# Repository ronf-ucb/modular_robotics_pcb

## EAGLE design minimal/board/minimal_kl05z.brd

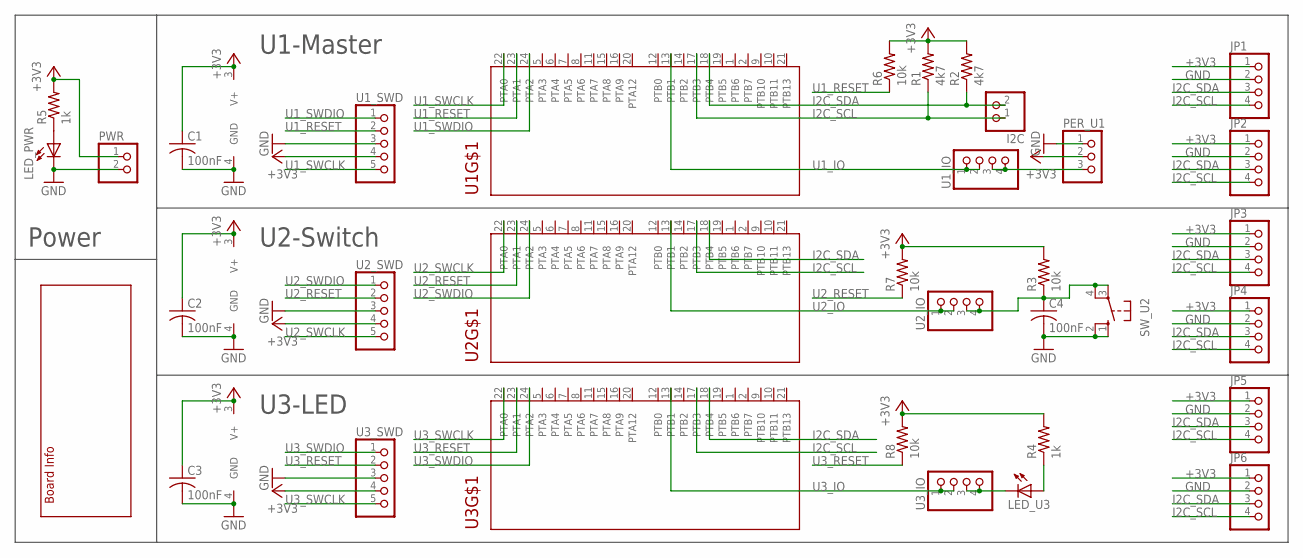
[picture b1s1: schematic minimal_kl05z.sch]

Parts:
C1, C2, C3, C4: 100nF; C025-025X050
I2C: PINHD-1X2; 1X02
JP1, JP2, JP3, JP4, JP5, JP6: PINHD-1X4; 1X04
LED_PWR: LED5MM
LED_U3: LED5MM
PER_U1: PINHD-1X3; 1X03
PWR: PINHD-1X2; 1X02
R1, R2: 4k7; 0204/7
R3: 10k; 0204V
R4, R5: 1k; 0204V
R6, R7, R8: 10k; 0204/7
SW_U2: 10-XX; B3F-10XX
U1, U2, U3: MKL05Z32VFK4-DIP; DIL24-3
U1_IO, U2_IO, U3_IO: PINHD-1X4; 1X04
U1_SWD, U2_SWD, U3_SWD: PINHD-1X5; 1X05
U$1: INFO

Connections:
+3V3: C1.1, C2.1, C3.1, JP1.1, JP2.1, JP3.1, JP4.1, JP5.1, JP6.1, PER_U1.2, PWR.1, R1.2, R2.2, R3.2, R4.2, R5.2, R6.2, R7.2, R8.2, U1.3 (V+), U1_SWD.4, U2.3 (V+), U2_SWD.4, U3.3 (V+), U3_SWD.4
GND: C1.2, C2.2, C3.2, C4.2, JP1.2, JP2.2, JP3.2, JP4.2, JP5.2, JP6.2, LED_PWR.K (C), PER_U1.1, PWR.2, SW_U2.1 (S), SW_U2.2 (S1), U1.4 (GND), U1_SWD.3, U2.4 (GND), U2_SWD.3, U3.4 (GND), U3_SWD.3
I2C_SCL: I2C.1, JP1.4, JP2.4, JP3.4, JP4.4, JP5.4, JP6.4, R1.1, U1.17 (PTB3), U2.17 (PTB3), U3.17 (PTB3)
I2C_SDA: I2C.2, JP1.3, JP2.3, JP3.3, JP4.3, JP5.3, JP6.3, R2.1, U1.18 (PTB4), U2.18 (PTB4), U3.18 (PTB4)
unnamed: LED_PWR.A, R5.1
unnamed: C4.1, R3.1, SW_U2.3, SW_U2.4 (P1), U2_IO.3, U2_IO.4
unnamed: PER_U1.3, U1_IO.3, U1_IO.4
unnamed: LED_U3.A, R4.1
unnamed: LED_U3.K (C), U3_IO.3, U3_IO.4
U1_IO: U1.13 (PTB1), U1_IO.1, U1_IO.2
U1_RESET: R6.1, U1.23 (PTA1), U1_SWD.2
U1_SWCLK: U1.22 (PTA0), U1_SWD.5
U1_SWDIO: U1.24 (PTA2), U1_SWD.1
U2_IO: U2.13 (PTB1), U2_IO.1, U2_IO.2
U2_RESET: R7.1, U2.23 (PTA1), U2_SWD.2
U2_SWCLK: U2.22 (PTA0), U2_SWD.5
U2_SWDIO: U2.24 (PTA2), U2_SWD.1
U3_IO: U3.13 (PTB1), U3_IO.1, U3_IO.2
U3_RESET: R8.1, U3.23 (PTA1), U3_SWD.2
U3_SWCLK: U3.22 (PTA0), U3_SWD.5
U3_SWDIO: U3.24 (PTA2), U3_SWD.1

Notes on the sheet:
U1-Master
U2-Switch
U3-LED
Power

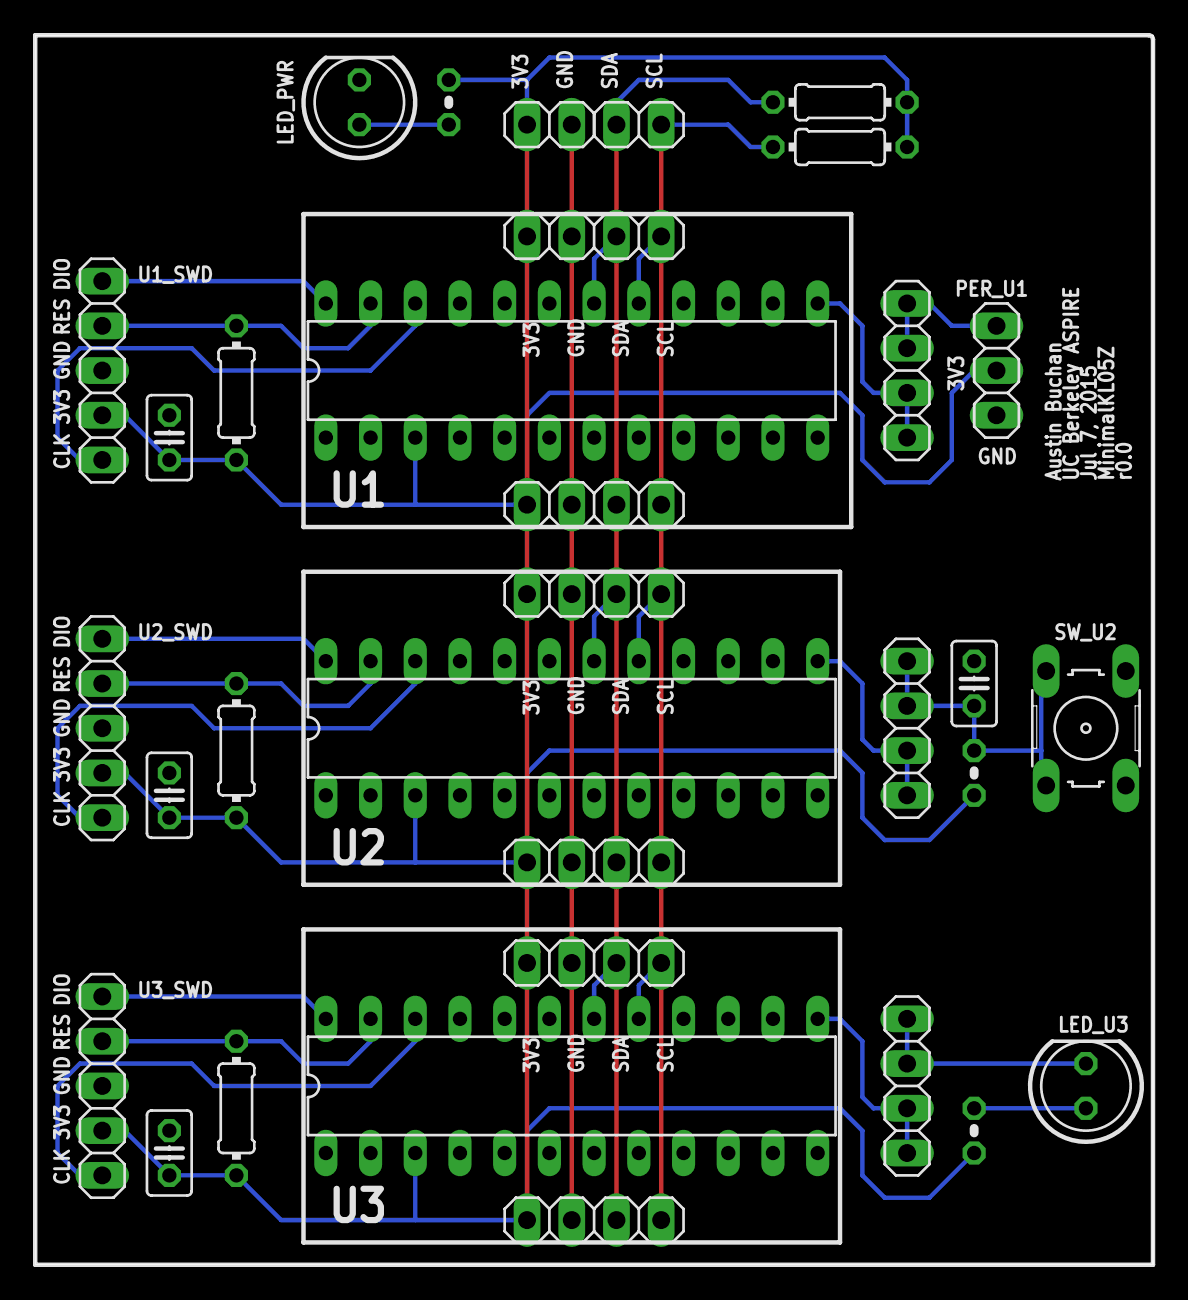
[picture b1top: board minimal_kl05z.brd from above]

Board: 2 copper layers, 63.5 x 69.8 mm, 34 parts (0 on the bottom side), 21 nets.

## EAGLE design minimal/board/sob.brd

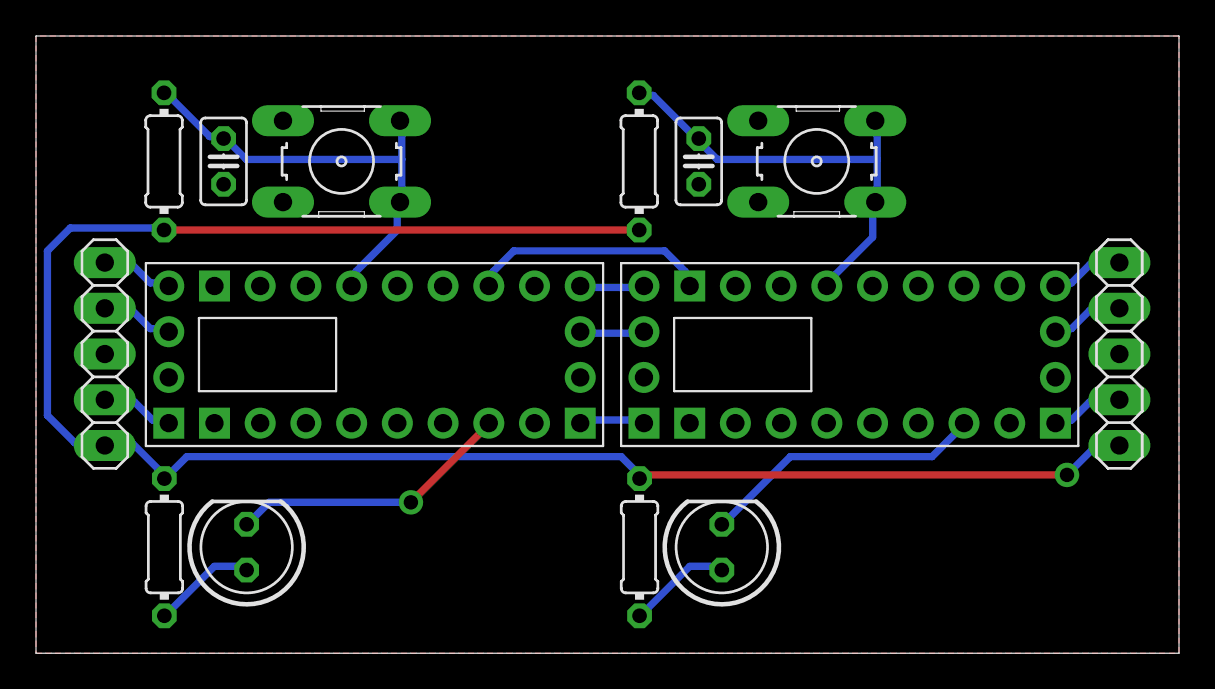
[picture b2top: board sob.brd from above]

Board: 2 copper layers, 63.5 x 34.3 mm, 14 parts (0 on the bottom side), 18 nets.

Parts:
C545, C622: 100nf; C025-025X050
CPU221, CPU610: CARRIER_DIP
LED552, LED629: LED5MM
R439, R597, R621, R630: 1k; 0204/7
SW339, SW620: B3F-10XX
SWD_L16: 1X05
SWD_R219: 1X05

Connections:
GND655: C545.1, C622.1, CPU221.GND_0, CPU221.GND_1, CPU221.PTB0, CPU610.GND_0, CPU610.GND_1, SW339.2, SW339.4, SW620.2, SW620.4, SWD_L16.3, SWD_R219.3
IO550: C545.2, CPU221.PTB5, R439.1, SW339.1, SW339.3
IO603: CPU221.PTB10, LED552.K
IO627: C622.2, CPU610.PTB5, R621.1, SW620.1, SW620.3
IO636: CPU610.PTB10, LED629.K
SCL01649: CPU221.SCL_1, CPU610.SCL_0
SCL_L643: CPU221.SCL_0, SWD_L16.4
SCL_R646: CPU610.SCL_1, SWD_R219.4
SDA01650: CPU221.SDA_1, CPU610.SDA_0
SDA_L644: CPU221.SDA_0, SWD_L16.5
SDA_R647: CPU610.SDA_1, SWD_R219.5
TOK01651: CPU221.PTB2, CPU610.PTB0
UP598: LED552.A, R597.1
UP631: LED629.A, R630.1
V3653: R439.2, R597.2, R621.2, R630.2, SWD_L16.1, SWD_R219.1
VCC01648: CPU221.VCC_1, CPU610.VCC_0
VCC_L642: CPU221.VCC_0, SWD_L16.2
VCC_R645: CPU610.VCC_1, SWD_R219.2

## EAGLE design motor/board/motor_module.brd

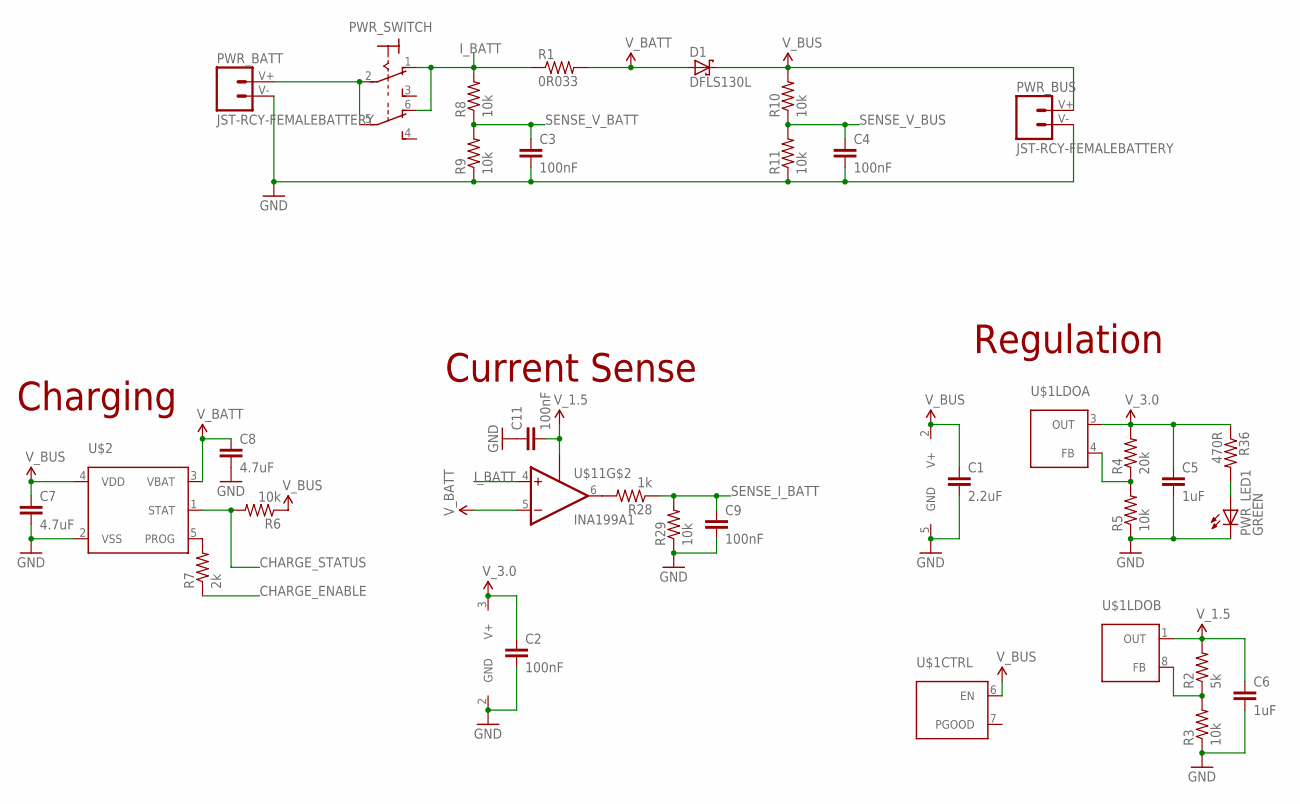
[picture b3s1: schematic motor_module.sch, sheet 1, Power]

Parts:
C1: 2.2uF; 0402-CAP
C2, C3, C4, C9, C11: 100nF; 0402-CAP
C5, C6: 1uF; 0402-CAP
C7, C8: 4.7uF; 0402-CAP
D1: DFLS130L; POWERDI123
PWR_BATT: JST-RCY-FEMALEBATTERY; TP_LIPO_160MAH
PWR_BUS: JST-RCY-FEMALEBATTERY; TP_LIPO_160MAH
PWR_LED1: GREEN; LED-0603
PWR_SWITCH: JS202011SCQN
R1: 0R033; 0603-RES
R2: 5k; 0402-RES
R3, R5, R6, R8, R9, R10, R11, R29: 10k; 0402-RES
R4: 20k; 0402-RES
R7: 2k; 0402-RES
R28: 1k; 0402-RES
R36: 470R; 0402-RES
U$1: SC560C; MLPQ-UT8
U$2: MCP73831T; SOT23-5
U$11: INA199A1; SC70-6

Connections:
CHARGE_ENABLE: R7.1; also elsewhere on the board
CHARGE_STATUS: R6.2, U$2.1 (STAT); also elsewhere on the board
GND: C1.2, C2.2, C3.2, C4.2, C5.2, C6.2, C7.2, C8.2, C9.2, C11.1, PWR_BATT.V- (1), PWR_BUS.V- (1), PWR_LED1.C, R3.1, R5.1, R9.1, R11.1, R29.1, U$1.5 (GND), U$2.2 (VSS), U$11.2 (GND); also elsewhere on the board
I_BATT: PWR_SWITCH.1 (O), PWR_SWITCH.6 (O), R1.1, R8.2, U$11.4 (+IN)
unnamed: PWR_BATT.V+ (2), PWR_SWITCH.2, PWR_SWITCH.5
unnamed: R2.1, R3.2, U$1.8 (FB)
unnamed: R4.1, R5.2, U$1.4 (FB)
unnamed: R7.2, U$2.5 (PROG)
unnamed: R28.2, U$11.6 (OUT)
unnamed: PWR_LED1.A, R36.2
SENSE_I_BATT: C9.1, R28.1, R29.2; also elsewhere on the board
SENSE_V_BATT: C3.1, R8.1, R9.2; also elsewhere on the board
SENSE_V_BUS: C4.1, R10.1, R11.2; also elsewhere on the board
V_1.5: C6.1, C11.2, R2.2, U$1.1 (OUT), U$11.1 (REF); also elsewhere on the board
V_3.0: C2.1, C5.1, R4.2, R36.1, U$1.3 (OUT), U$11.3 (V+); also elsewhere on the board
V_BATT: C8.1, D1.A, R1.2, U$2.3 (VBAT), U$11.5 (-IN); also elsewhere on the board
V_BUS: C1.1, C7.1, D1.C, PWR_BUS.V+ (2), R6.1, R10.2, U$1.2 (V+), U$1.6 (EN), U$2.4 (VDD)

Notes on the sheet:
Charging
Current Sense
Regulation

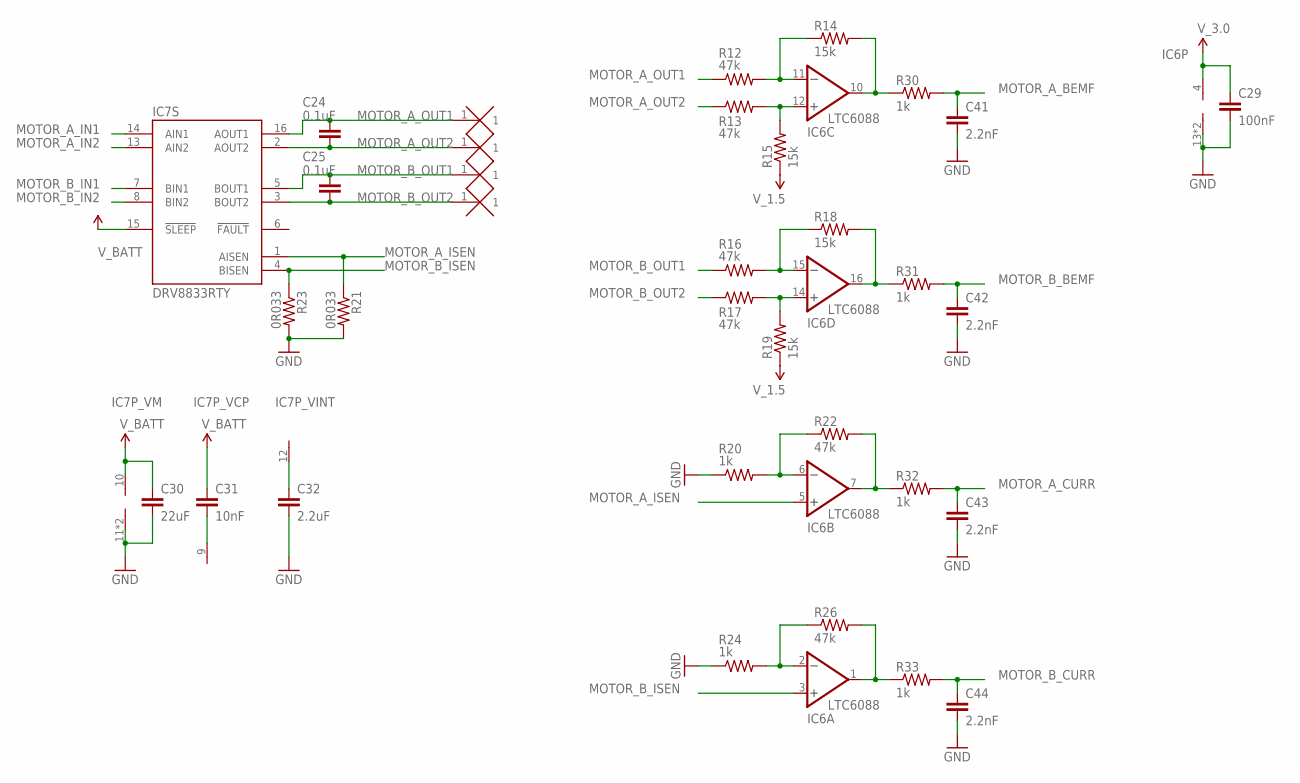
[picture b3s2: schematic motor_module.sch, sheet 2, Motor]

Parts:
C24, C25: 0.1uF; 0402-CAP; VOLTAGE 10V
C29: 100nF; 0402-CAP
C30: 22uF; 0603-CAP
C31: 10nF; 0402-CAP; VOLTAGE 16V
C32: 2.2uF; 0402-CAP; VOLTAGE 6.3V
C41, C42, C43, C44: 2.2nF; 0402-CAP
IC6: LTC6088; DFN-16
IC7: DRV8833RTY; S-PWQFN-N16
MA1, MA2: PAD-0.6_1.8; PAD_0.6_1.8
MB1, MB2: PAD-0.6_1.8; PAD_0.6_1.8
R12, R13, R16, R17, R22, R26: 47k; 0402-RES; TOLERANCE 1%
R14, R15, R18, R19: 15k; 0402-RES; TOLERANCE 1%
R20, R24: 1k; 0402-RES; TOLERANCE 1%
R21, R23: 0R033; 0603-RES
R30, R31, R32, R33: 1k; 0402-RES

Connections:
GND: C29.2, C30.2, C32.2, C41.2, C42.2, C43.2, C44.2, IC6.13 (V-), IC6.PAD (V-), IC7.11 (V-), IC7.PPAD (V-), R20.1, R21.2, R23.2, R24.1; also elsewhere on the board
MOTOR_A_BEMF: C41.1, R30.2; also elsewhere on the board
MOTOR_A_CURR: C43.1, R32.2; also elsewhere on the board
MOTOR_A_IN1: IC7.14 (AIN1); also elsewhere on the board
MOTOR_A_IN2: IC7.13 (AIN2); also elsewhere on the board
MOTOR_A_ISEN: IC6.5 (+IN), IC7.1 (AISEN), R21.1
MOTOR_A_OUT1: C24.1, IC7.16 (AOUT1), MA1.1, R12.1
MOTOR_A_OUT2: C24.2, IC7.2 (AOUT2), MA2.1, R13.1
MOTOR_B_BEMF: C42.1, R31.2; also elsewhere on the board
MOTOR_B_CURR: C44.1, R33.2; also elsewhere on the board
MOTOR_B_IN1: IC7.7 (BIN1); also elsewhere on the board
MOTOR_B_IN2: IC7.8 (BIN2); also elsewhere on the board
MOTOR_B_ISEN: IC6.3 (+IN), IC7.4 (BISEN), R23.1
MOTOR_B_OUT1: C25.1, IC7.5 (BOUT1), MB1.1, R16.1
MOTOR_B_OUT2: C25.2, IC7.3 (BOUT2), MB2.1, R17.1
unnamed: C31.2, IC7.9 (V+)
unnamed: C32.1, IC7.12 (V-)
unnamed: IC6.15 (-IN), R16.2, R18.1
unnamed: IC6.14 (+IN), R17.2, R19.2
unnamed: IC6.6 (-IN), R20.2, R22.1
unnamed: IC6.2 (-IN), R24.2, R26.1
unnamed: IC6.11 (-IN), R12.2, R14.1
unnamed: IC6.12 (+IN), R13.2, R15.2
unnamed: IC6.1 (OUT), R26.2, R33.1
unnamed: IC6.7 (OUT), R22.2, R32.1
unnamed: IC6.10 (OUT), R14.2, R30.1
unnamed: IC6.16 (OUT), R18.2, R31.1
V_1.5: R15.1, R19.1; also elsewhere on the board
V_3.0: C29.1, IC6.4 (V+); also elsewhere on the board
V_BATT: C30.1, C31.1, IC7.10 (V+), IC7.15 (!SLEEP); also elsewhere on the board

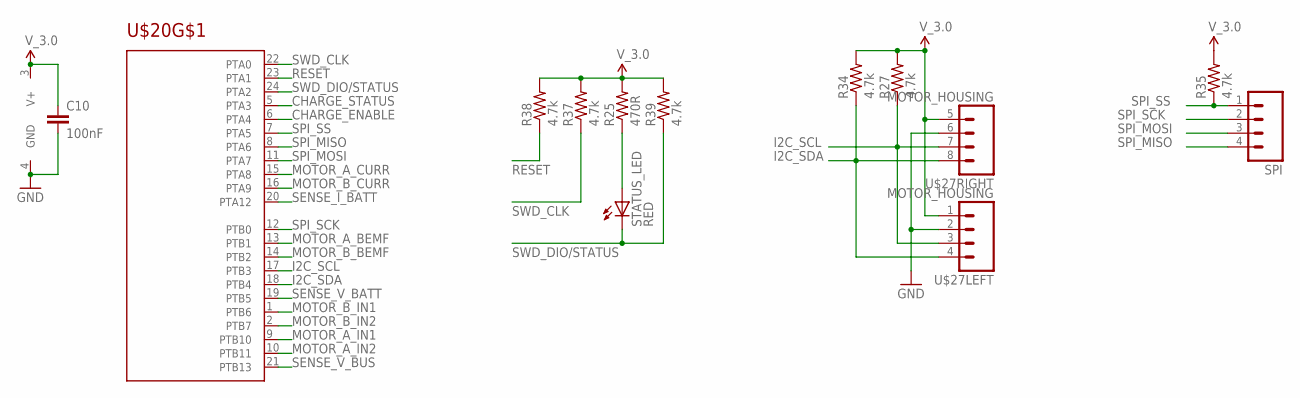
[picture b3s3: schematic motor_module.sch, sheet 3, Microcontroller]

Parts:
C10: 100nF; 0402-CAP
R25: 470R; 0402-RES
R27, R34, R35, R37, R38, R39: 4.7k; 0402-RES
SPI: M04FFC; MOLEX_503480-0400
STATUS_LED: RED; LED-0603
U$20: MKL05Z32VFK4; QFN-24
U$27: MOTOR_HOUSING

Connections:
CHARGE_ENABLE: U$20.6 (PTA4); also elsewhere on the board
CHARGE_STATUS: U$20.5 (PTA3); also elsewhere on the board
GND: C10.2, U$20.4 (GND), U$27.2, U$27.6 (2); also elsewhere on the board
I2C_SCL: R27.1, U$20.17 (PTB3), U$27.3, U$27.7 (3)
I2C_SDA: R34.1, U$20.18 (PTB4), U$27.4, U$27.8 (4)
MOTOR_A_BEMF: U$20.13 (PTB1); also elsewhere on the board
MOTOR_A_CURR: U$20.15 (PTA8); also elsewhere on the board
MOTOR_A_IN1: U$20.9 (PTB10); also elsewhere on the board
MOTOR_A_IN2: U$20.10 (PTB11); also elsewhere on the board
MOTOR_B_BEMF: U$20.14 (PTB2); also elsewhere on the board
MOTOR_B_CURR: U$20.16 (PTA9); also elsewhere on the board
MOTOR_B_IN1: U$20.1 (PTB6); also elsewhere on the board
MOTOR_B_IN2: U$20.2 (PTB7); also elsewhere on the board
unnamed: R25.1, STATUS_LED.A
RESET: R38.1, U$20.23 (PTA1)
SENSE_I_BATT: U$20.20 (PTA12); also elsewhere on the board
SENSE_V_BATT: U$20.19 (PTB5); also elsewhere on the board
SENSE_V_BUS: U$20.21 (PTB13); also elsewhere on the board
SPI_MISO: SPI.4, U$20.8 (PTA6)
SPI_MOSI: SPI.3, U$20.11 (PTA7)
SPI_SCK: SPI.2, U$20.12 (PTB0)
SPI_SS: R35.1, SPI.1, U$20.7 (PTA5)
SWD_CLK: R37.1, U$20.22 (PTA0)
SWD_DIO/STATUS: R39.1, STATUS_LED.C, U$20.24 (PTA2)
V_3.0: C10.1, R25.2, R27.2, R34.2, R35.2, R37.2, R38.2, R39.2, U$20.3 (V+), U$27.1, U$27.5 (1); also elsewhere on the board

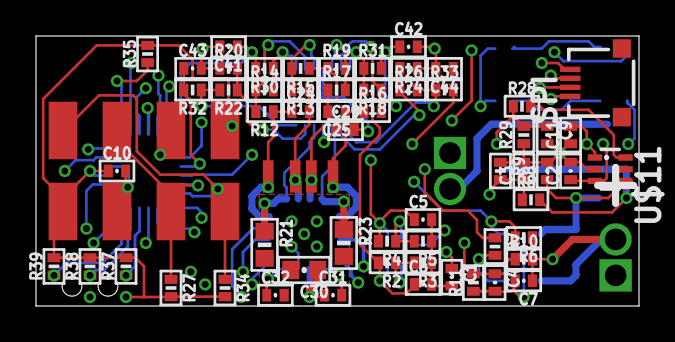
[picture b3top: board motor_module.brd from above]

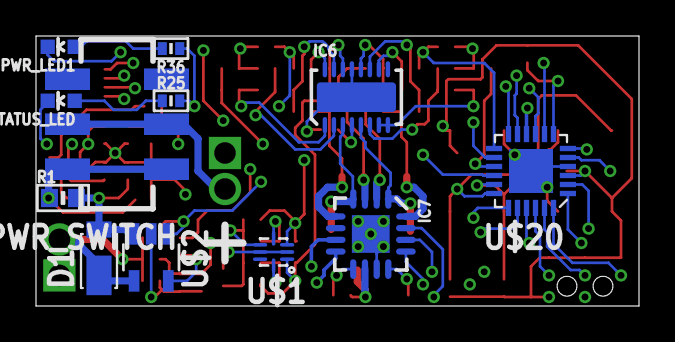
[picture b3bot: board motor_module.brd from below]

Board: 4 copper layers, 33.5 x 15.0 mm, 78 parts (13 on the bottom side), 53 nets.

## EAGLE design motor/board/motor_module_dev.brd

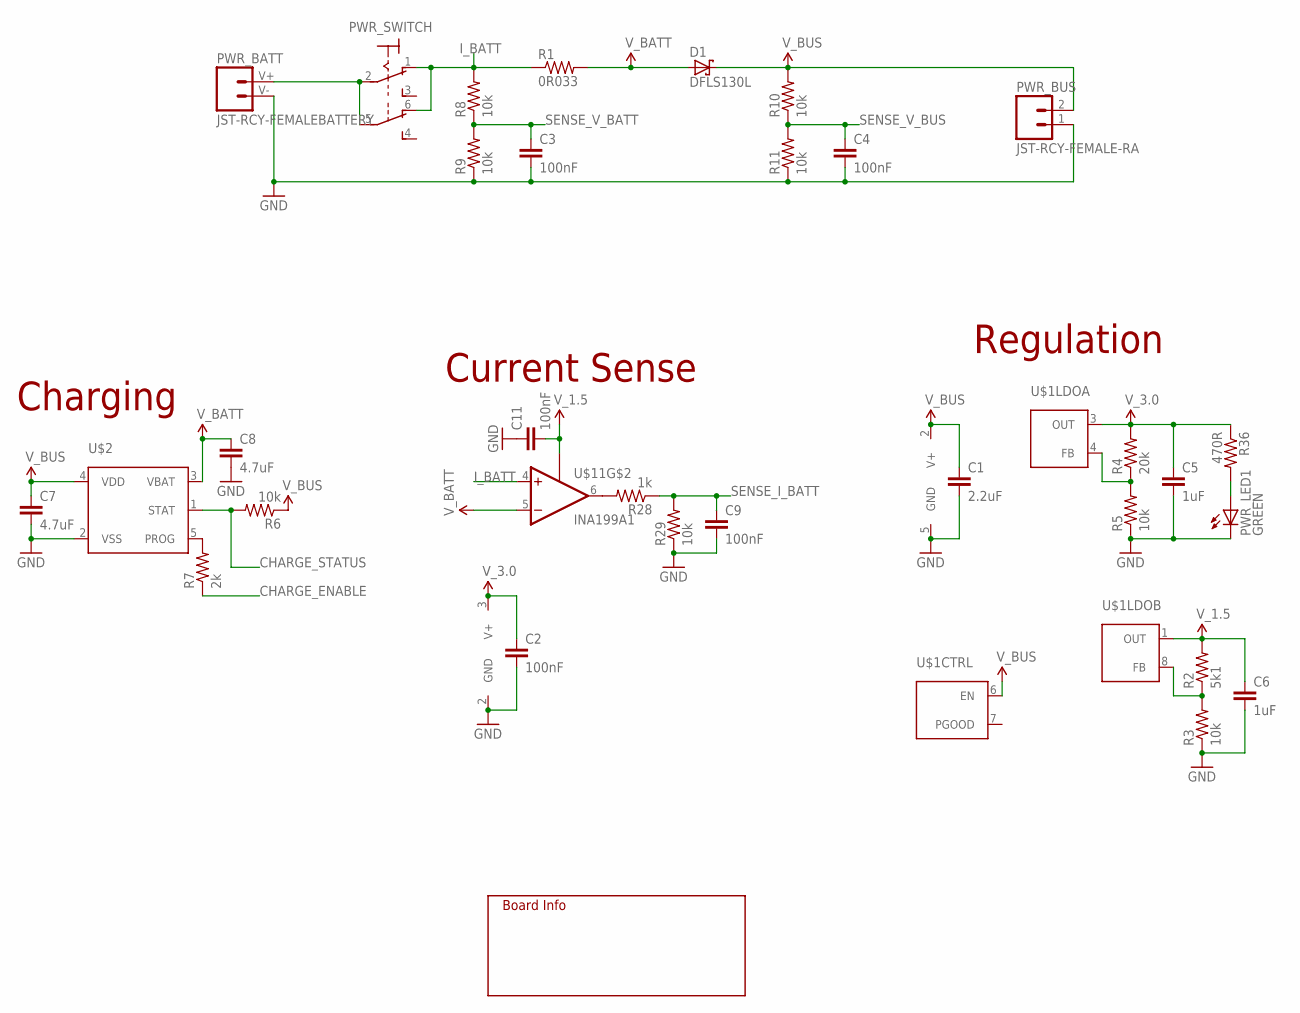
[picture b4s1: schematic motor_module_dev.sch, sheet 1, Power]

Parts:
C1: 2.2uF; 0402-CAP; VOLTAGE 10V
C2, C3, C4, C9, C11: 100nF; 0402-CAP; VOLTAGE 6.3V
C5, C6: 1uF; 0402-CAP; VOLTAGE 6.3V
C7, C8: 4.7uF; 0402-CAP; VOLTAGE 10V
D1: DFLS130L; POWERDI123
PWR_BATT: JST-RCY-FEMALEBATTERY; TP_LIPO_160MAH
PWR_BUS: JST-RCY-FEMALE-RA; JST_2_FEMALE
PWR_LED1: GREEN; LED-0603
PWR_SWITCH: JS202011SCQN
R1: 0R033; 0603-RES
R2: 5k1; 0402-RES
R3, R5, R6, R8, R9, R10, R11, R29: 10k; 0402-RES
R4: 20k; 0402-RES
R7: 2k; 0402-RES
R28: 1k; 0402-RES
R36: 470R; 0402-RES
U$1: SC560C; MLPQ-UT8
U$2: MCP73831T; SOT23-5
U$11: INA199A1; SC70-6
U$31: INFO

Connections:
CHARGE_ENABLE: R7.1; also elsewhere on the board
CHARGE_STATUS: R6.2, U$2.1 (STAT); also elsewhere on the board
GND: C1.2, C2.2, C3.2, C4.2, C5.2, C6.2, C7.2, C8.2, C9.2, C11.1, PWR_BATT.V- (1), PWR_BUS.1, PWR_LED1.C, R3.1, R5.1, R9.1, R11.1, R29.1, U$1.5 (GND), U$2.2 (VSS), U$11.2 (GND); also elsewhere on the board
I_BATT: PWR_SWITCH.1 (O), PWR_SWITCH.6 (O), R1.1, R8.2, U$11.4 (+IN)
unnamed: PWR_BATT.V+ (2), PWR_SWITCH.2, PWR_SWITCH.5
unnamed: R2.1, R3.2, U$1.8 (FB)
unnamed: R4.1, R5.2, U$1.4 (FB)
unnamed: R7.2, U$2.5 (PROG)
unnamed: R28.2, U$11.6 (OUT)
unnamed: PWR_LED1.A, R36.2
SENSE_I_BATT: C9.1, R28.1, R29.2; also elsewhere on the board
SENSE_V_BATT: C3.1, R8.1, R9.2; also elsewhere on the board
SENSE_V_BUS: C4.1, R10.1, R11.2; also elsewhere on the board
V_1.5: C6.1, C11.2, R2.2, U$1.1 (OUT), U$11.1 (REF); also elsewhere on the board
V_3.0: C2.1, C5.1, R4.2, R36.1, U$1.3 (OUT), U$11.3 (V+); also elsewhere on the board
V_BATT: C8.1, D1.A, R1.2, U$2.3 (VBAT), U$11.5 (-IN); also elsewhere on the board
V_BUS: C1.1, C7.1, D1.C, PWR_BUS.2, R6.1, R10.2, U$1.2 (V+), U$1.6 (EN), U$2.4 (VDD); also elsewhere on the board

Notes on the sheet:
Charging
Current Sense
Regulation

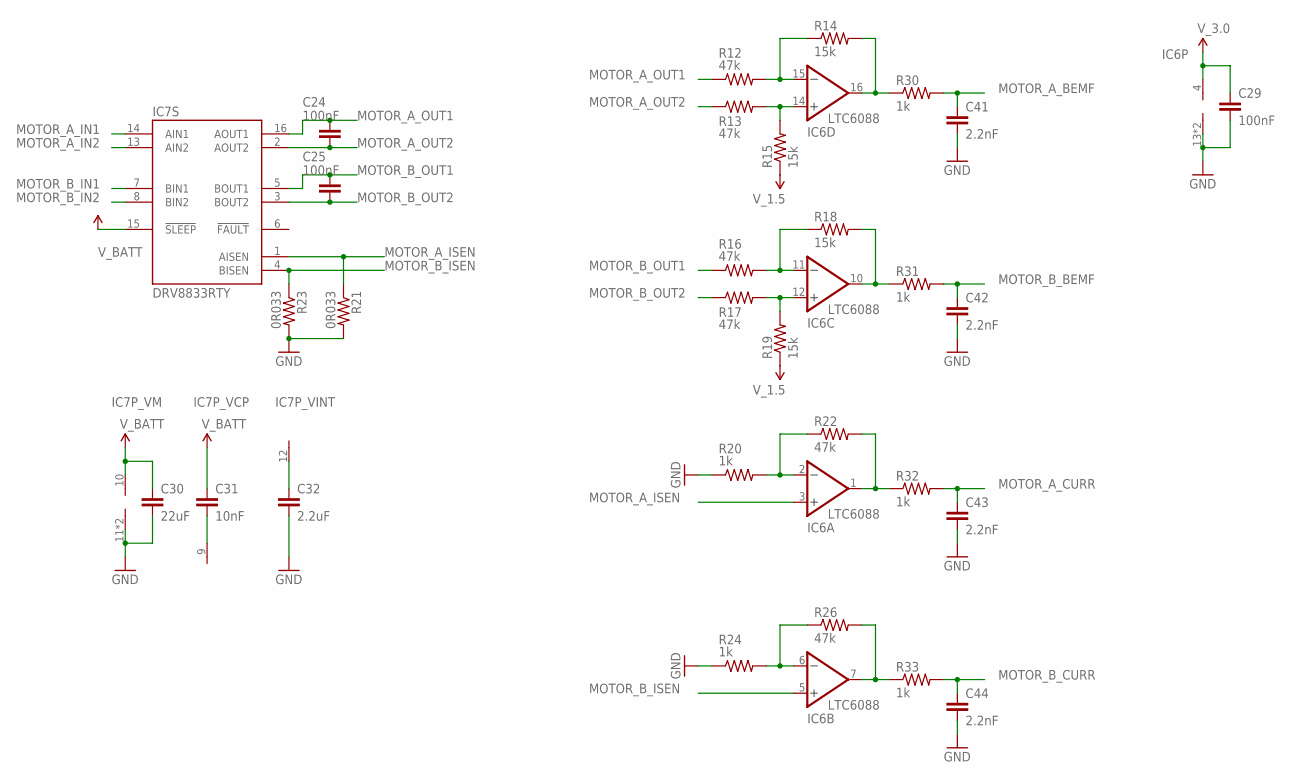
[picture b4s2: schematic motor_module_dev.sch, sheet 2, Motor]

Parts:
C24, C25: 100nF; 0402-CAP; VOLTAGE 10V
C29: 100nF; 0402-CAP; VOLTAGE 6.3V
C30: 22uF; 0603-CAP; VOLTAGE 10V
C31: 10nF; 0402-CAP; VOLTAGE 16V
C32: 2.2uF; 0402-CAP; VOLTAGE 6.3V
C41, C42, C43, C44: 2.2nF; 0402-CAP; VOLTAGE 6.3V
IC6: LTC6088; DFN-16
IC7: DRV8833RTY; S-PWQFN-N16
R12, R13, R16, R17, R22, R26: 47k; 0402-RES; TOLERANCE 1%
R14, R15, R18, R19: 15k; 0402-RES; TOLERANCE 1%
R20, R24: 1k; 0402-RES; TOLERANCE 1%
R21, R23: 0R033; 0603-RES
R30, R31, R32, R33: 1k; 0402-RES

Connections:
GND: C29.2, C30.2, C32.2, C41.2, C42.2, C43.2, C44.2, IC6.13 (V-), IC6.PAD (V-), IC7.11 (V-), IC7.PPAD (V-), R20.1, R21.2, R23.2, R24.1; also elsewhere on the board
MOTOR_A_BEMF: C41.1, R30.2; also elsewhere on the board
MOTOR_A_CURR: C43.1, R32.2; also elsewhere on the board
MOTOR_A_IN1: IC7.14 (AIN1); also elsewhere on the board
MOTOR_A_IN2: IC7.13 (AIN2); also elsewhere on the board
MOTOR_A_ISEN: IC6.3 (+IN), IC7.1 (AISEN), R21.1
MOTOR_A_OUT1: C24.1, IC7.16 (AOUT1), R12.1
MOTOR_A_OUT2: C24.2, IC7.2 (AOUT2), R13.1
MOTOR_B_BEMF: C42.1, R31.2; also elsewhere on the board
MOTOR_B_CURR: C44.1, R33.2; also elsewhere on the board
MOTOR_B_IN1: IC7.7 (BIN1); also elsewhere on the board
MOTOR_B_IN2: IC7.8 (BIN2); also elsewhere on the board
MOTOR_B_ISEN: IC6.5 (+IN), IC7.4 (BISEN), R23.1
MOTOR_B_OUT1: C25.1, IC7.5 (BOUT1), R16.1
MOTOR_B_OUT2: C25.2, IC7.3 (BOUT2), R17.1
unnamed: C31.2, IC7.9 (V+)
unnamed: C32.1, IC7.12 (V-)
unnamed: IC6.11 (-IN), R16.2, R18.1
unnamed: IC6.12 (+IN), R17.2, R19.2
unnamed: IC6.2 (-IN), R20.2, R22.1
unnamed: IC6.6 (-IN), R24.2, R26.1
unnamed: IC6.15 (-IN), R12.2, R14.1
unnamed: IC6.14 (+IN), R13.2, R15.2
unnamed: IC6.7 (OUT), R26.2, R33.1
unnamed: IC6.1 (OUT), R22.2, R32.1
unnamed: IC6.16 (OUT), R14.2, R30.1
unnamed: IC6.10 (OUT), R18.2, R31.1
V_1.5: R15.1, R19.1; also elsewhere on the board
V_3.0: C29.1, IC6.4 (V+); also elsewhere on the board
V_BATT: C30.1, C31.1, IC7.10 (V+), IC7.15 (!SLEEP); also elsewhere on the board

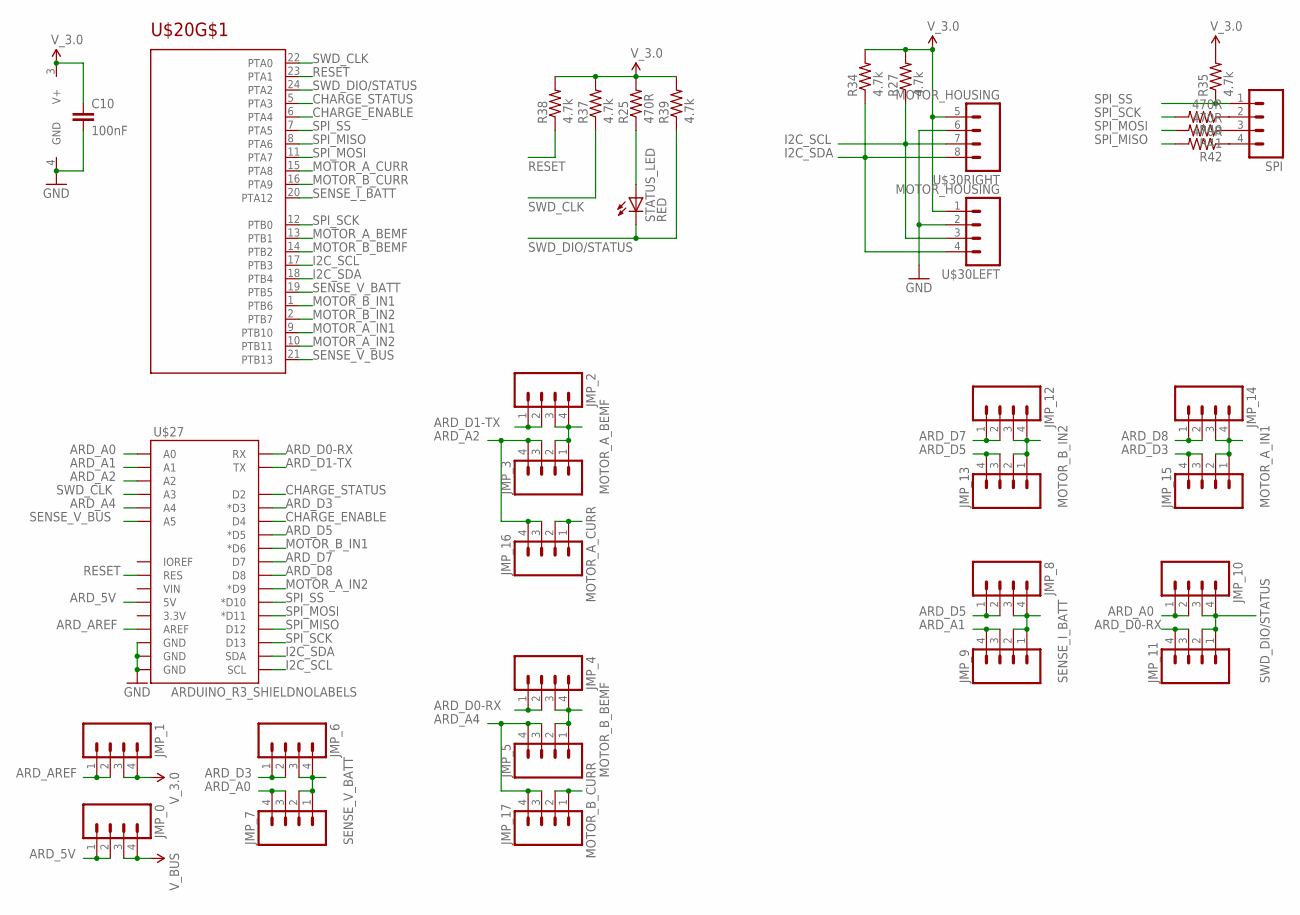
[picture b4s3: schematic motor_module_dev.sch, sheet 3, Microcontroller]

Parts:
C10: 100nF; 0402-CAP; VOLTAGE 6.3V
JMP_0, JMP_1, JMP_2, JMP_3, JMP_4, JMP_5, JMP_6, JMP_7, JMP_8, JMP_9, JMP_10, JMP_11, JMP_12, JMP_13, JMP_14, JMP_15, JMP_16, JMP_17: M041X04_NO_SILK; 1X04_NO_SILK
R25, R40, R41, R42: 470R; 0402-RES
R27, R34, R35, R37, R38, R39: 4.7k; 0402-RES
SPI: M041X04_NO_SILK; 1X04_NO_SILK
STATUS_LED: RED; LED-0603
U$20: MKL05Z32VFK4; QFN-24
U$27: ARDUINO_R3_SHIELDNOLABELS; UNO_R3_SHIELD_NOLABELS
U$30: MOTOR_HOUSING

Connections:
ARD_5V: JMP_0.1, JMP_0.2, U$27.5V
ARD_A0: JMP_7.3, JMP_7.4, JMP_10.1, JMP_10.2, U$27.A0
ARD_A1: JMP_9.3, JMP_9.4, U$27.A1
ARD_A2: JMP_3.3, JMP_3.4, JMP_16.3, JMP_16.4, U$27.A2
ARD_A4: JMP_5.3, JMP_5.4, JMP_17.3, JMP_17.4, U$27.A4
ARD_AREF: JMP_1.1, JMP_1.2, U$27.AREF
ARD_D0-RX: JMP_4.1, JMP_4.2, JMP_11.3, JMP_11.4, U$27.RX
ARD_D1-TX: JMP_2.1, JMP_2.2, U$27.TX
ARD_D3: JMP_6.1, JMP_6.2, JMP_15.3, JMP_15.4, U$27.D3 (*D3)
ARD_D5: JMP_8.1, JMP_8.2, JMP_13.3, JMP_13.4, U$27.D5 (*D5)
ARD_D7: JMP_12.1, JMP_12.2, U$27.D7
ARD_D8: JMP_14.1, JMP_14.2, U$27.D8
CHARGE_ENABLE: U$20.6 (PTA4), U$27.D4; also elsewhere on the board
CHARGE_STATUS: U$20.5 (PTA3), U$27.D2; also elsewhere on the board
GND: C10.2, U$20.4 (GND), U$27.GND@0 (GND), U$27.GND@1 (GND), U$27.GND@2 (GND), U$30.2, U$30.6 (2); also elsewhere on the board
I2C_SCL: R27.1, U$20.17 (PTB3), U$27.SCL, U$30.3, U$30.7 (3)
I2C_SDA: R34.1, U$20.18 (PTB4), U$27.SDA, U$30.4, U$30.8 (4)
MOTOR_A_BEMF: JMP_2.3, JMP_2.4, JMP_3.1, JMP_3.2, U$20.13 (PTB1); also elsewhere on the board
MOTOR_A_CURR: JMP_16.1, JMP_16.2, U$20.15 (PTA8); also elsewhere on the board
MOTOR_A_IN1: JMP_14.3, JMP_14.4, JMP_15.1, JMP_15.2, U$20.9 (PTB10); also elsewhere on the board
MOTOR_A_IN2: U$20.10 (PTB11), U$27.D9 (*D9); also elsewhere on the board
MOTOR_B_BEMF: JMP_4.3, JMP_4.4, JMP_5.1, JMP_5.2, U$20.14 (PTB2); also elsewhere on the board
MOTOR_B_CURR: JMP_17.1, JMP_17.2, U$20.16 (PTA9); also elsewhere on the board
MOTOR_B_IN1: U$20.1 (PTB6), U$27.D6 (*D6); also elsewhere on the board
MOTOR_B_IN2: JMP_12.3, JMP_12.4, JMP_13.1, JMP_13.2, U$20.2 (PTB7); also elsewhere on the board
unnamed: R25.1, STATUS_LED.A
unnamed: R40.1, SPI.2
unnamed: R41.1, SPI.3
unnamed: R42.1, SPI.4
RESET: R38.1, U$20.23 (PTA1), U$27.RES
SENSE_I_BATT: JMP_8.3, JMP_8.4, JMP_9.1, JMP_9.2, U$20.20 (PTA12); also elsewhere on the board
SENSE_V_BATT: JMP_6.3, JMP_6.4, JMP_7.1, JMP_7.2, U$20.19 (PTB5); also elsewhere on the board
SENSE_V_BUS: U$20.21 (PTB13), U$27.A5; also elsewhere on the board
SPI_MISO: R42.2, U$20.8 (PTA6), U$27.D12
SPI_MOSI: R41.2, U$20.11 (PTA7), U$27.D11 (*D11)
SPI_SCK: R40.2, U$20.12 (PTB0), U$27.D13
SPI_SS: R35.1, SPI.1, U$20.7 (PTA5), U$27.D10 (*D10)
SWD_CLK: R37.1, U$20.22 (PTA0), U$27.A3
SWD_DIO/STATUS: JMP_10.3, JMP_10.4, JMP_11.1, JMP_11.2, R39.1, STATUS_LED.C, U$20.24 (PTA2)
V_3.0: C10.1, JMP_1.3, JMP_1.4, R25.2, R27.2, R34.2, R35.2, R37.2, R38.2, R39.2, U$20.3 (V+), U$30.1, U$30.5 (1); also elsewhere on the board
V_BUS: JMP_0.3, JMP_0.4; also elsewhere on the board

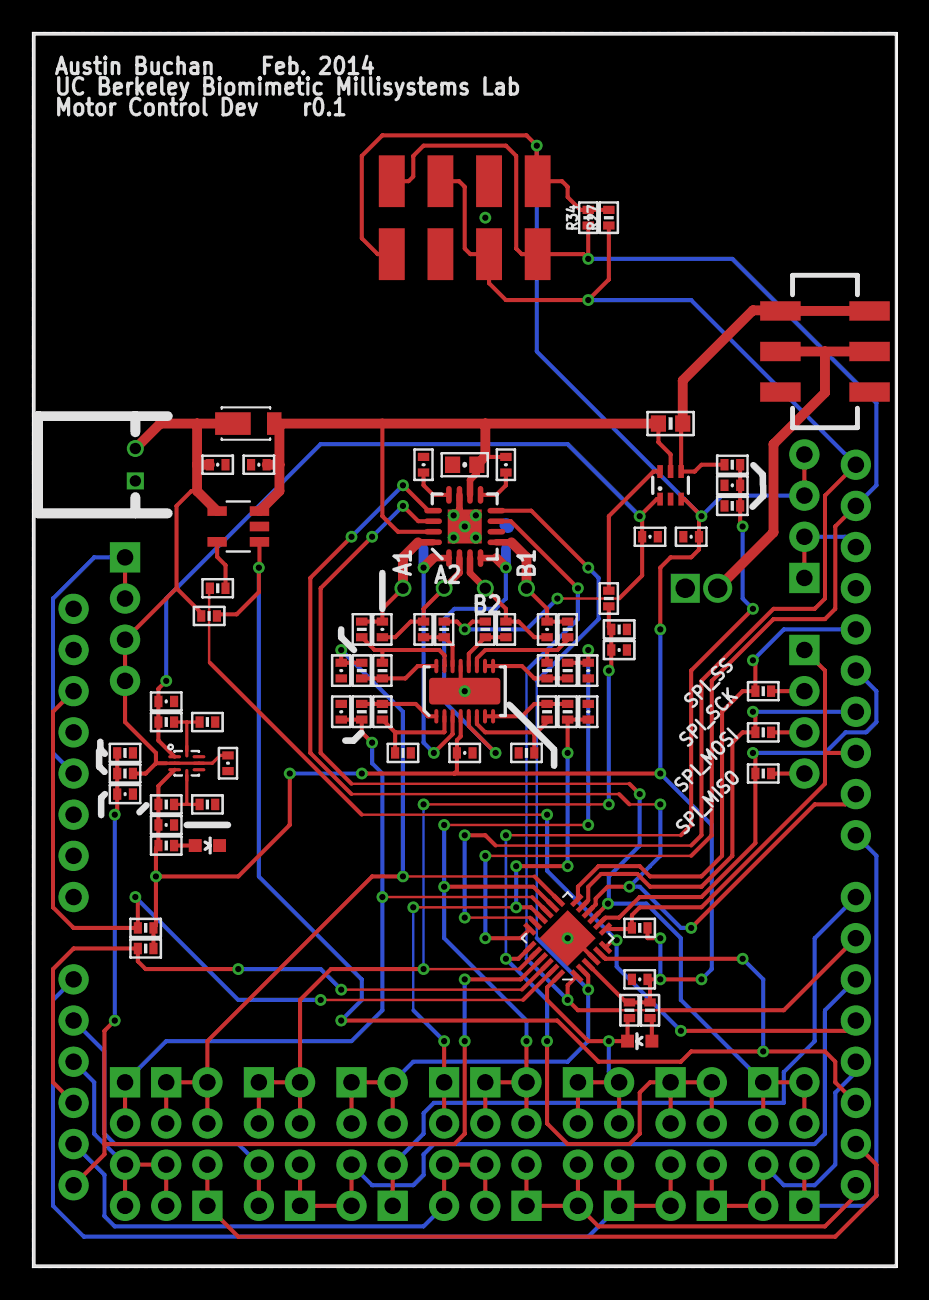
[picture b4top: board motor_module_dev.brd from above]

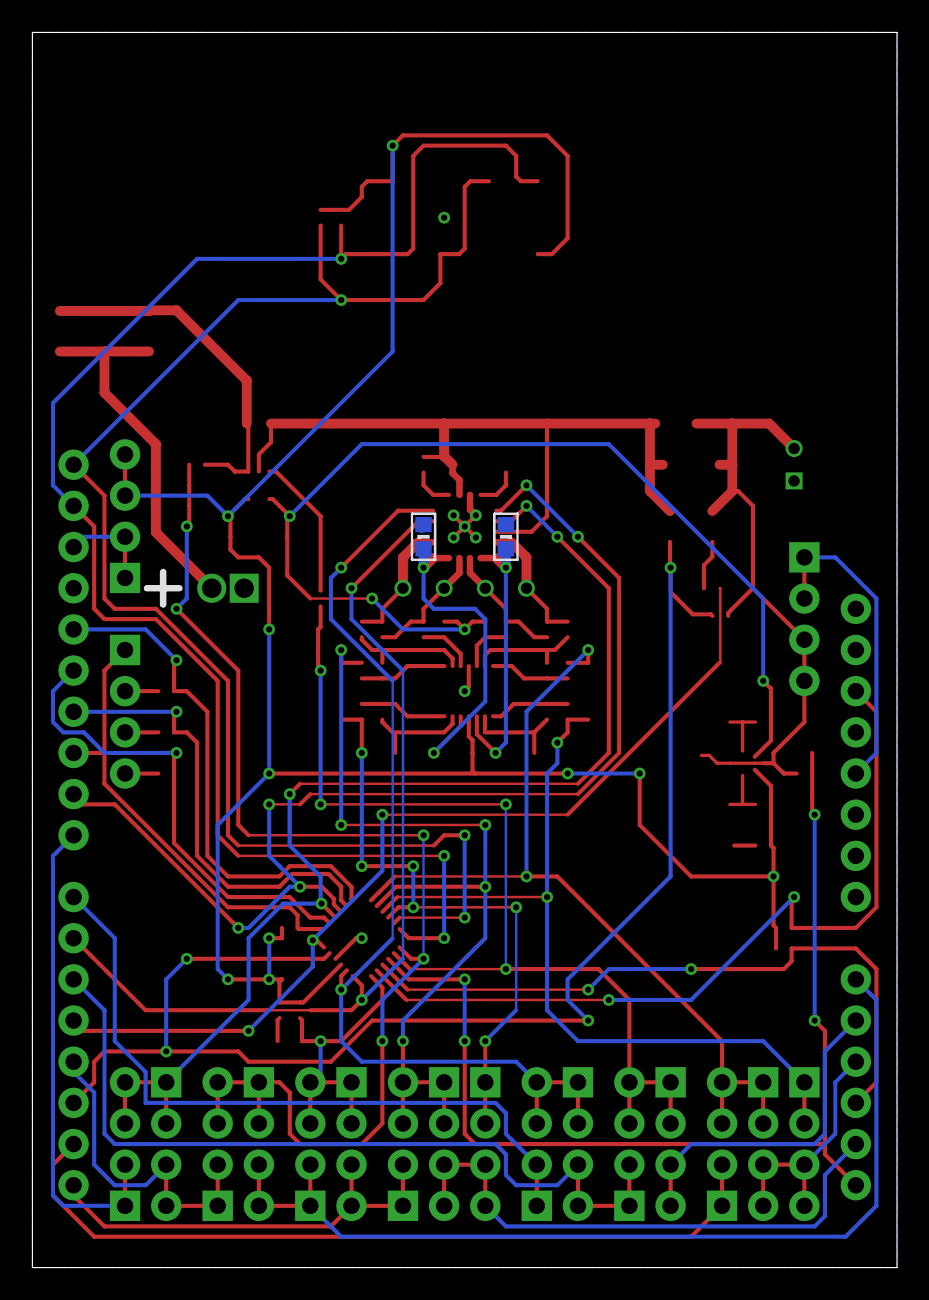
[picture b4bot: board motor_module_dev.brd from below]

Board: 4 copper layers, 53.3 x 76.2 mm, 97 parts (3 on the bottom side), 68 nets.

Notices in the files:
parts and their libraries:
biomimetic: UC Regents. All rights reserved.
SparkFun-Boards: Licensing: CC v3.0 Share-Alike You are welcome to use this library for commercial purposes.
SparkFun-Passives: Licensing: Creative Commons ShareAlike 4.0 International - https://creativecommons.org/licenses/by-sa/4.0
